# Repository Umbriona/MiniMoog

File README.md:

# MiniMoog
Minimoog clone project

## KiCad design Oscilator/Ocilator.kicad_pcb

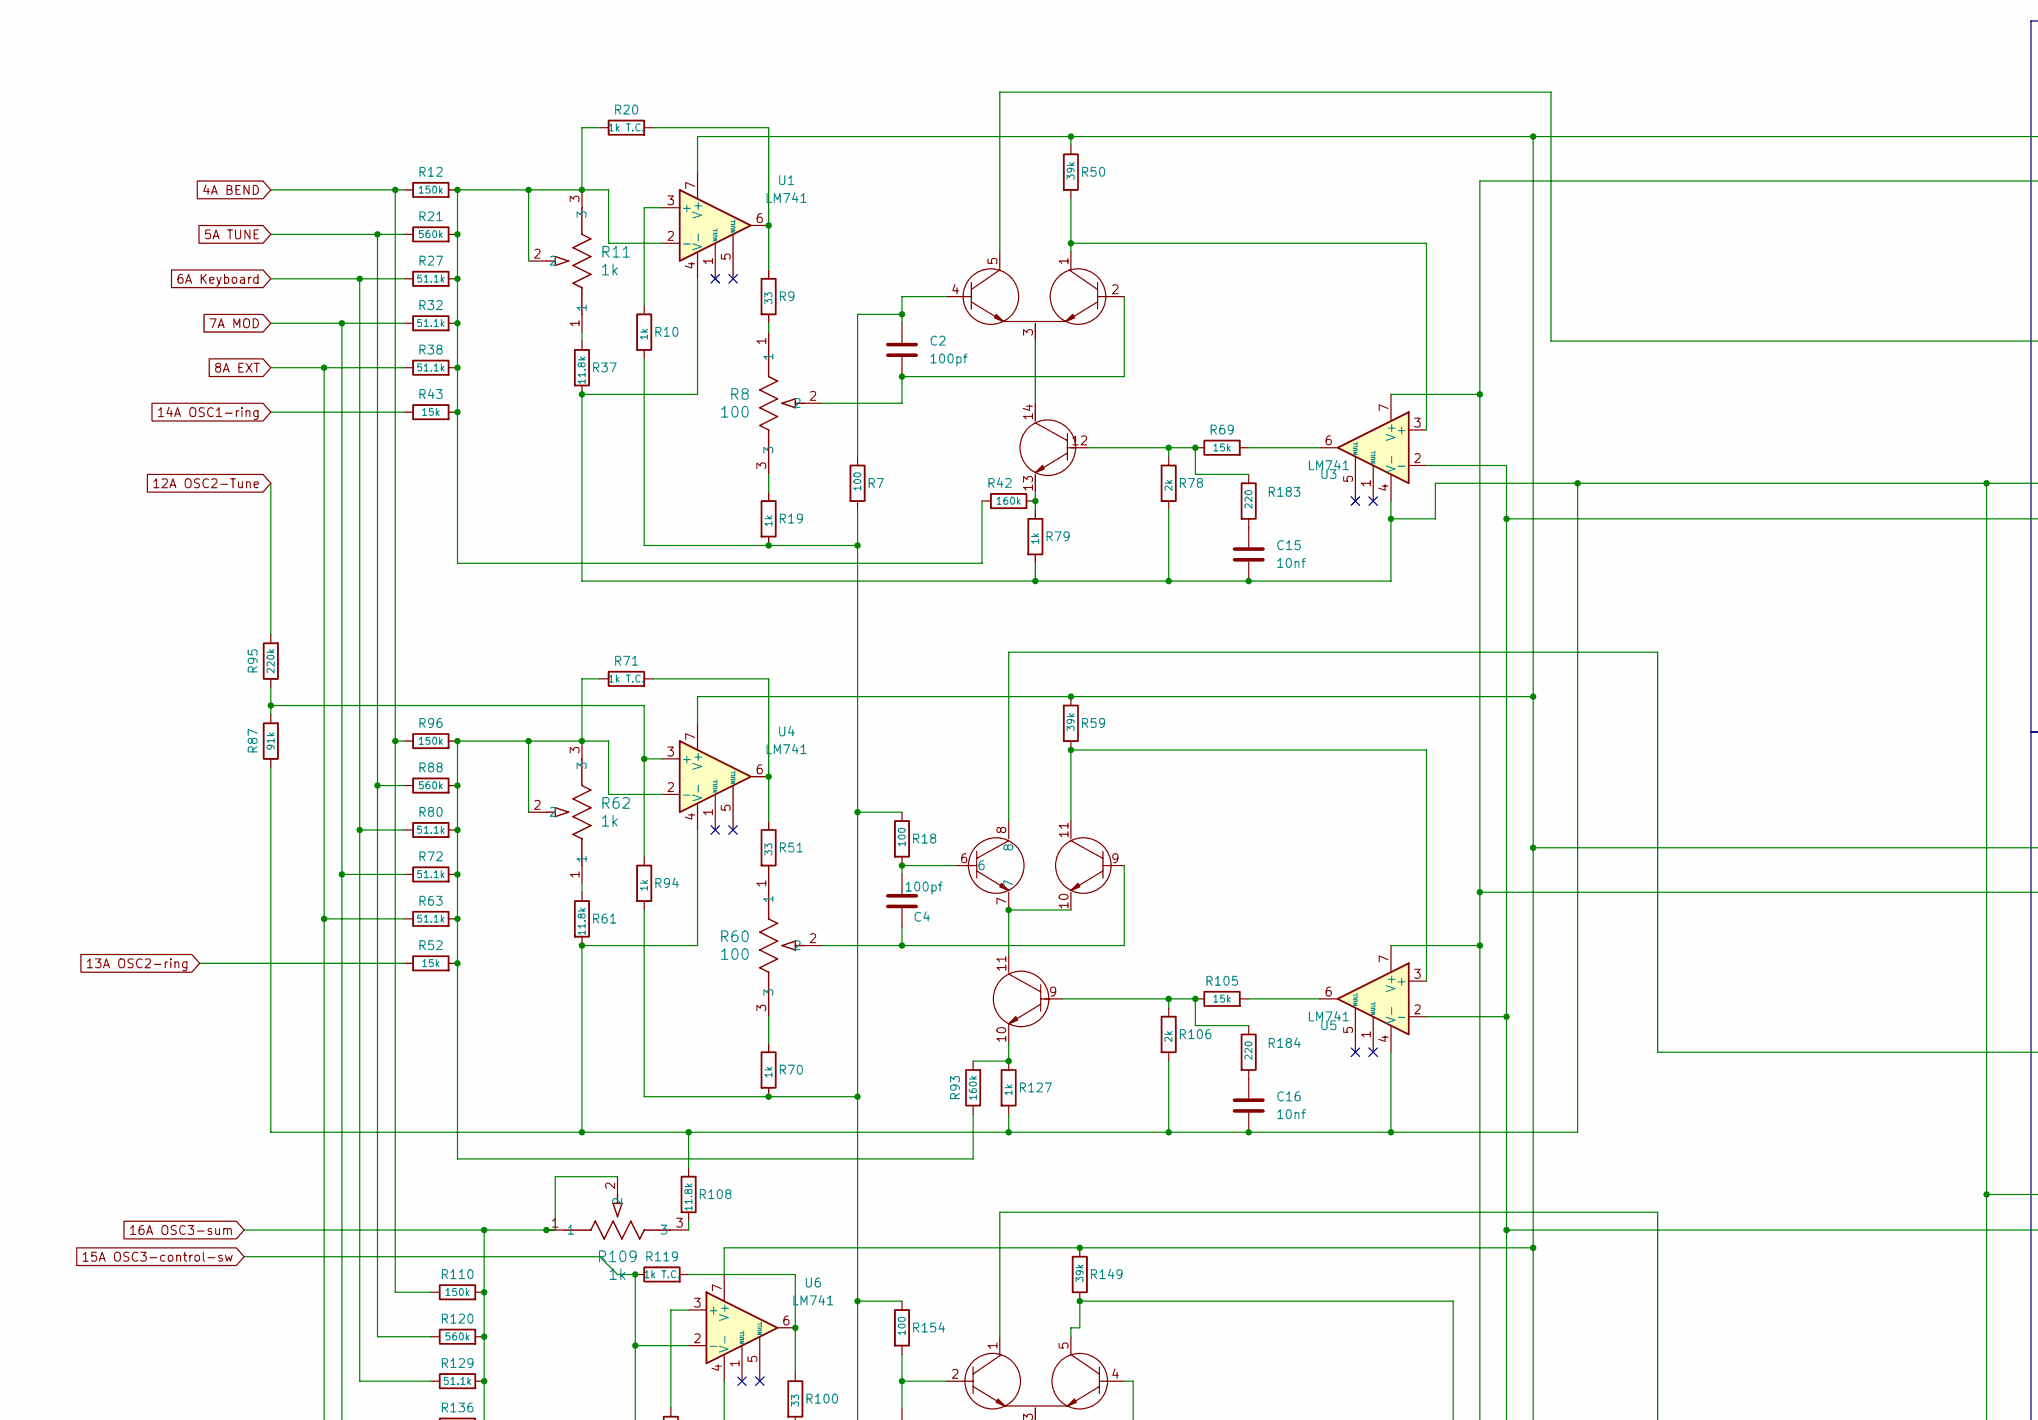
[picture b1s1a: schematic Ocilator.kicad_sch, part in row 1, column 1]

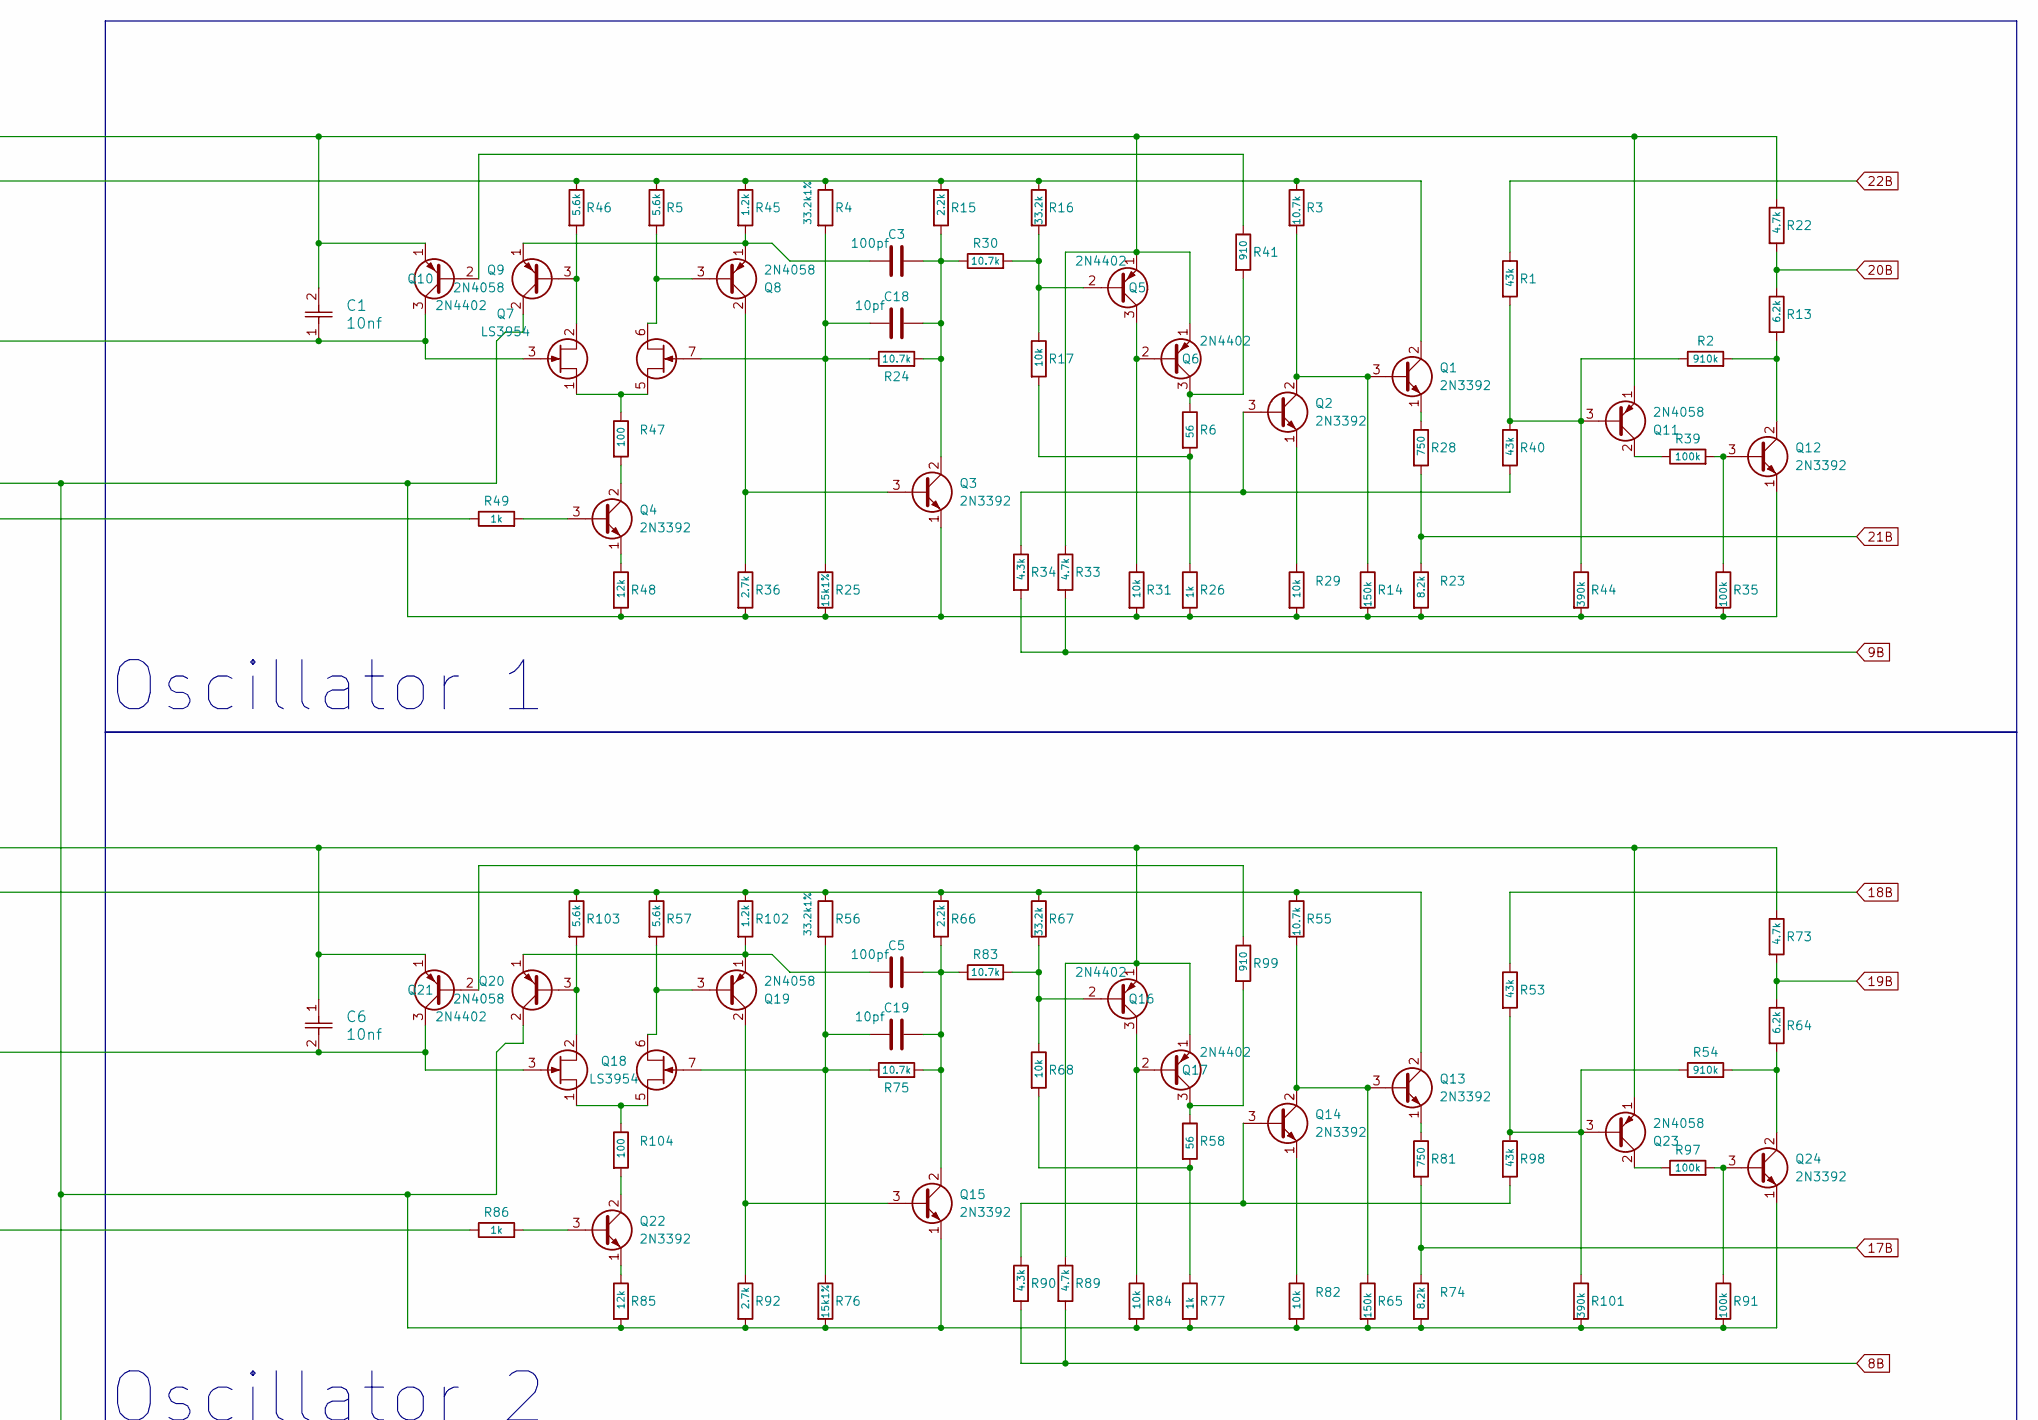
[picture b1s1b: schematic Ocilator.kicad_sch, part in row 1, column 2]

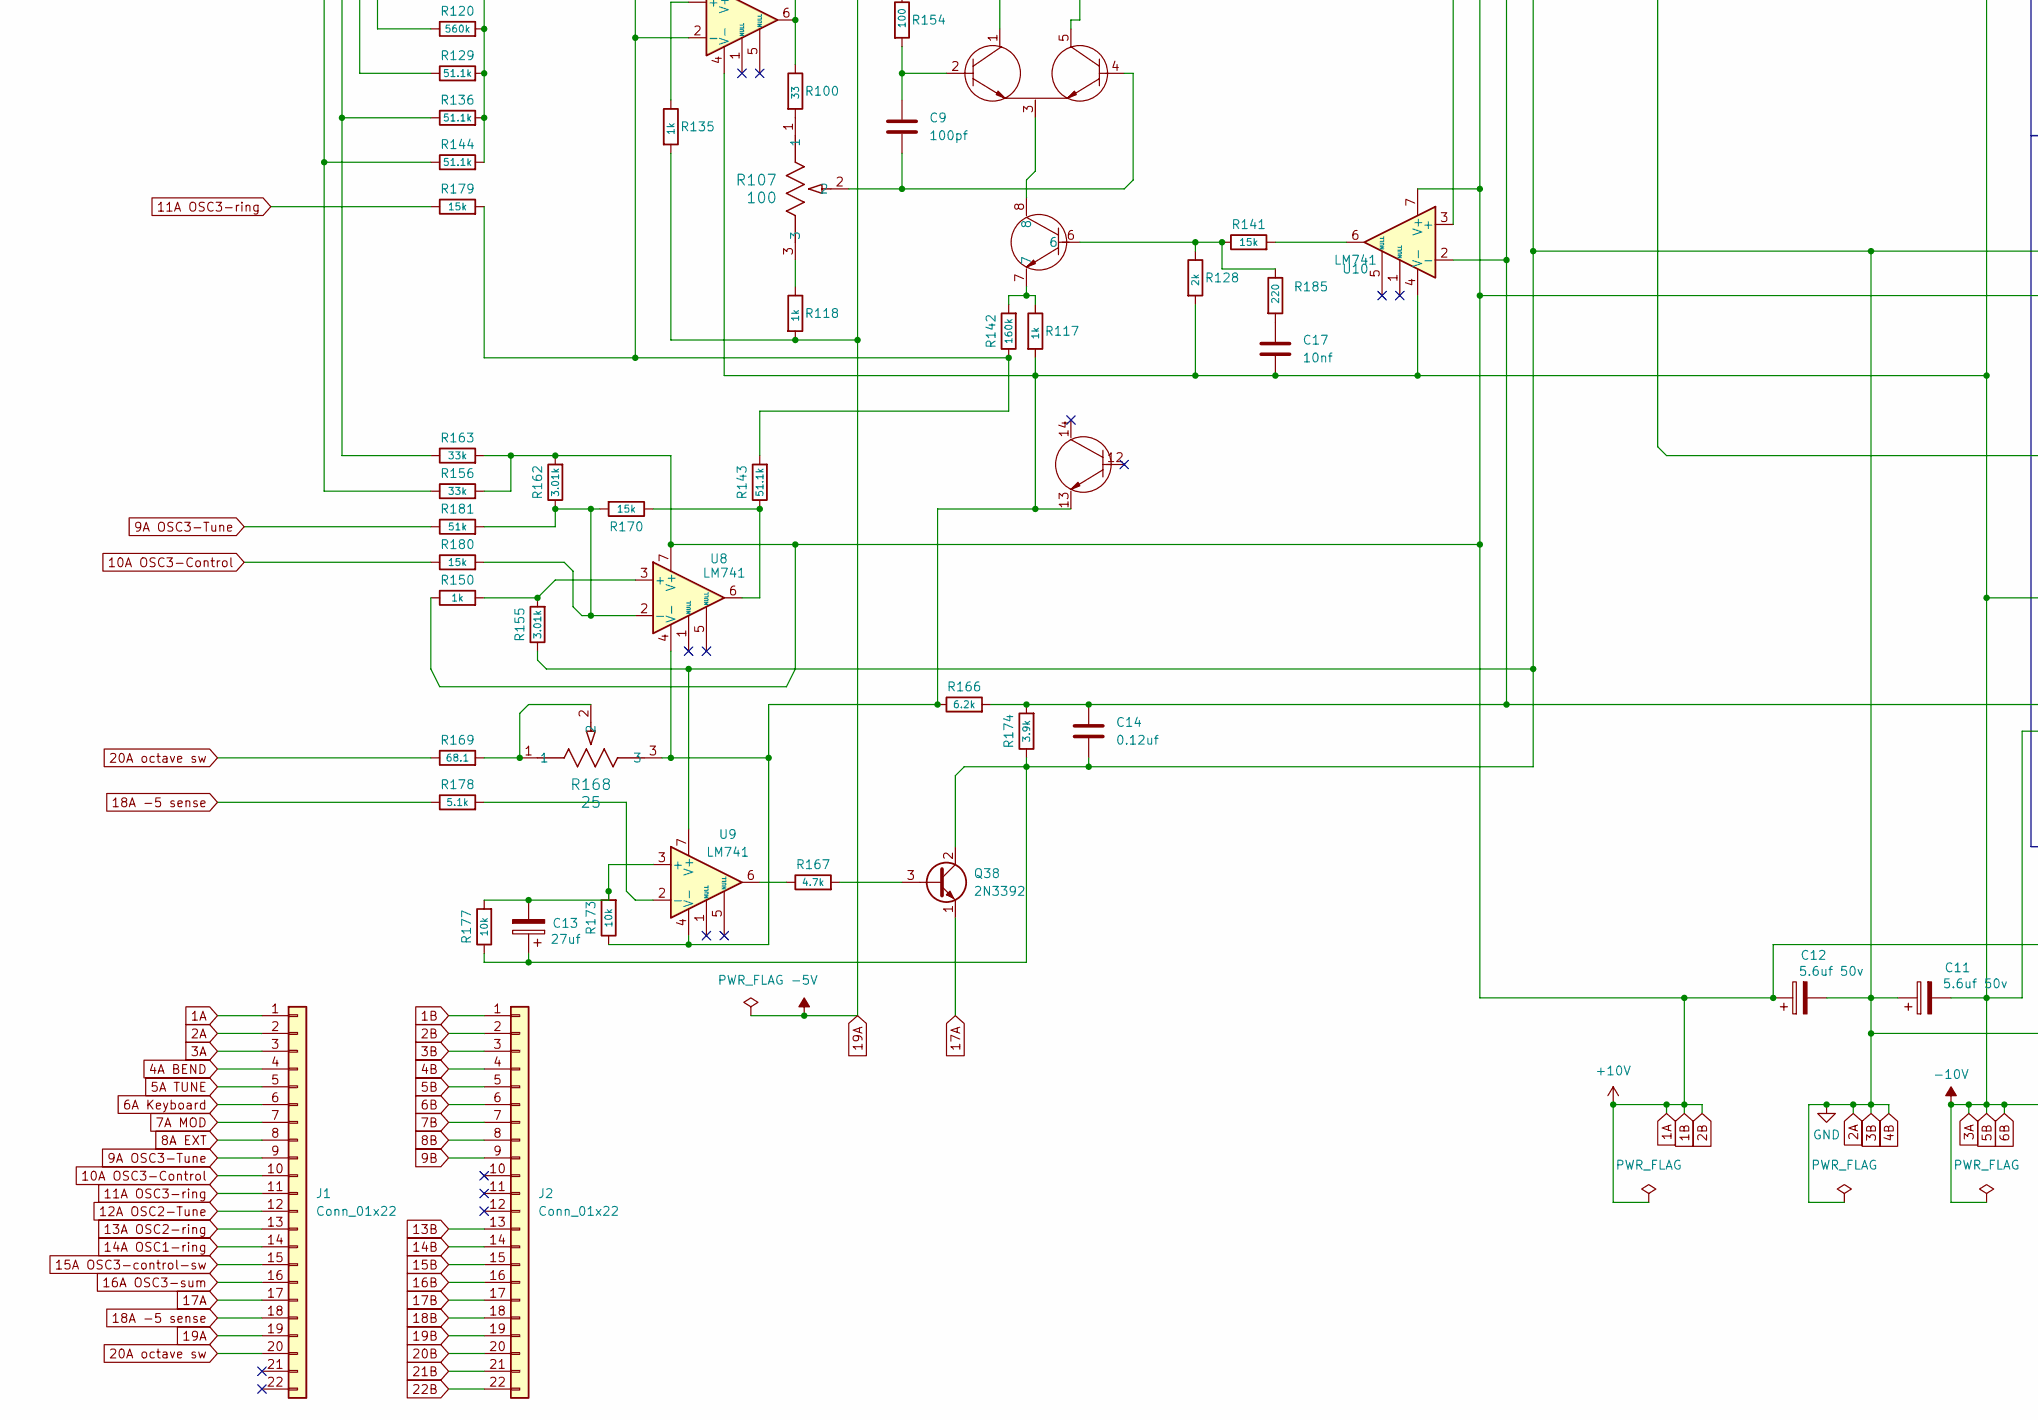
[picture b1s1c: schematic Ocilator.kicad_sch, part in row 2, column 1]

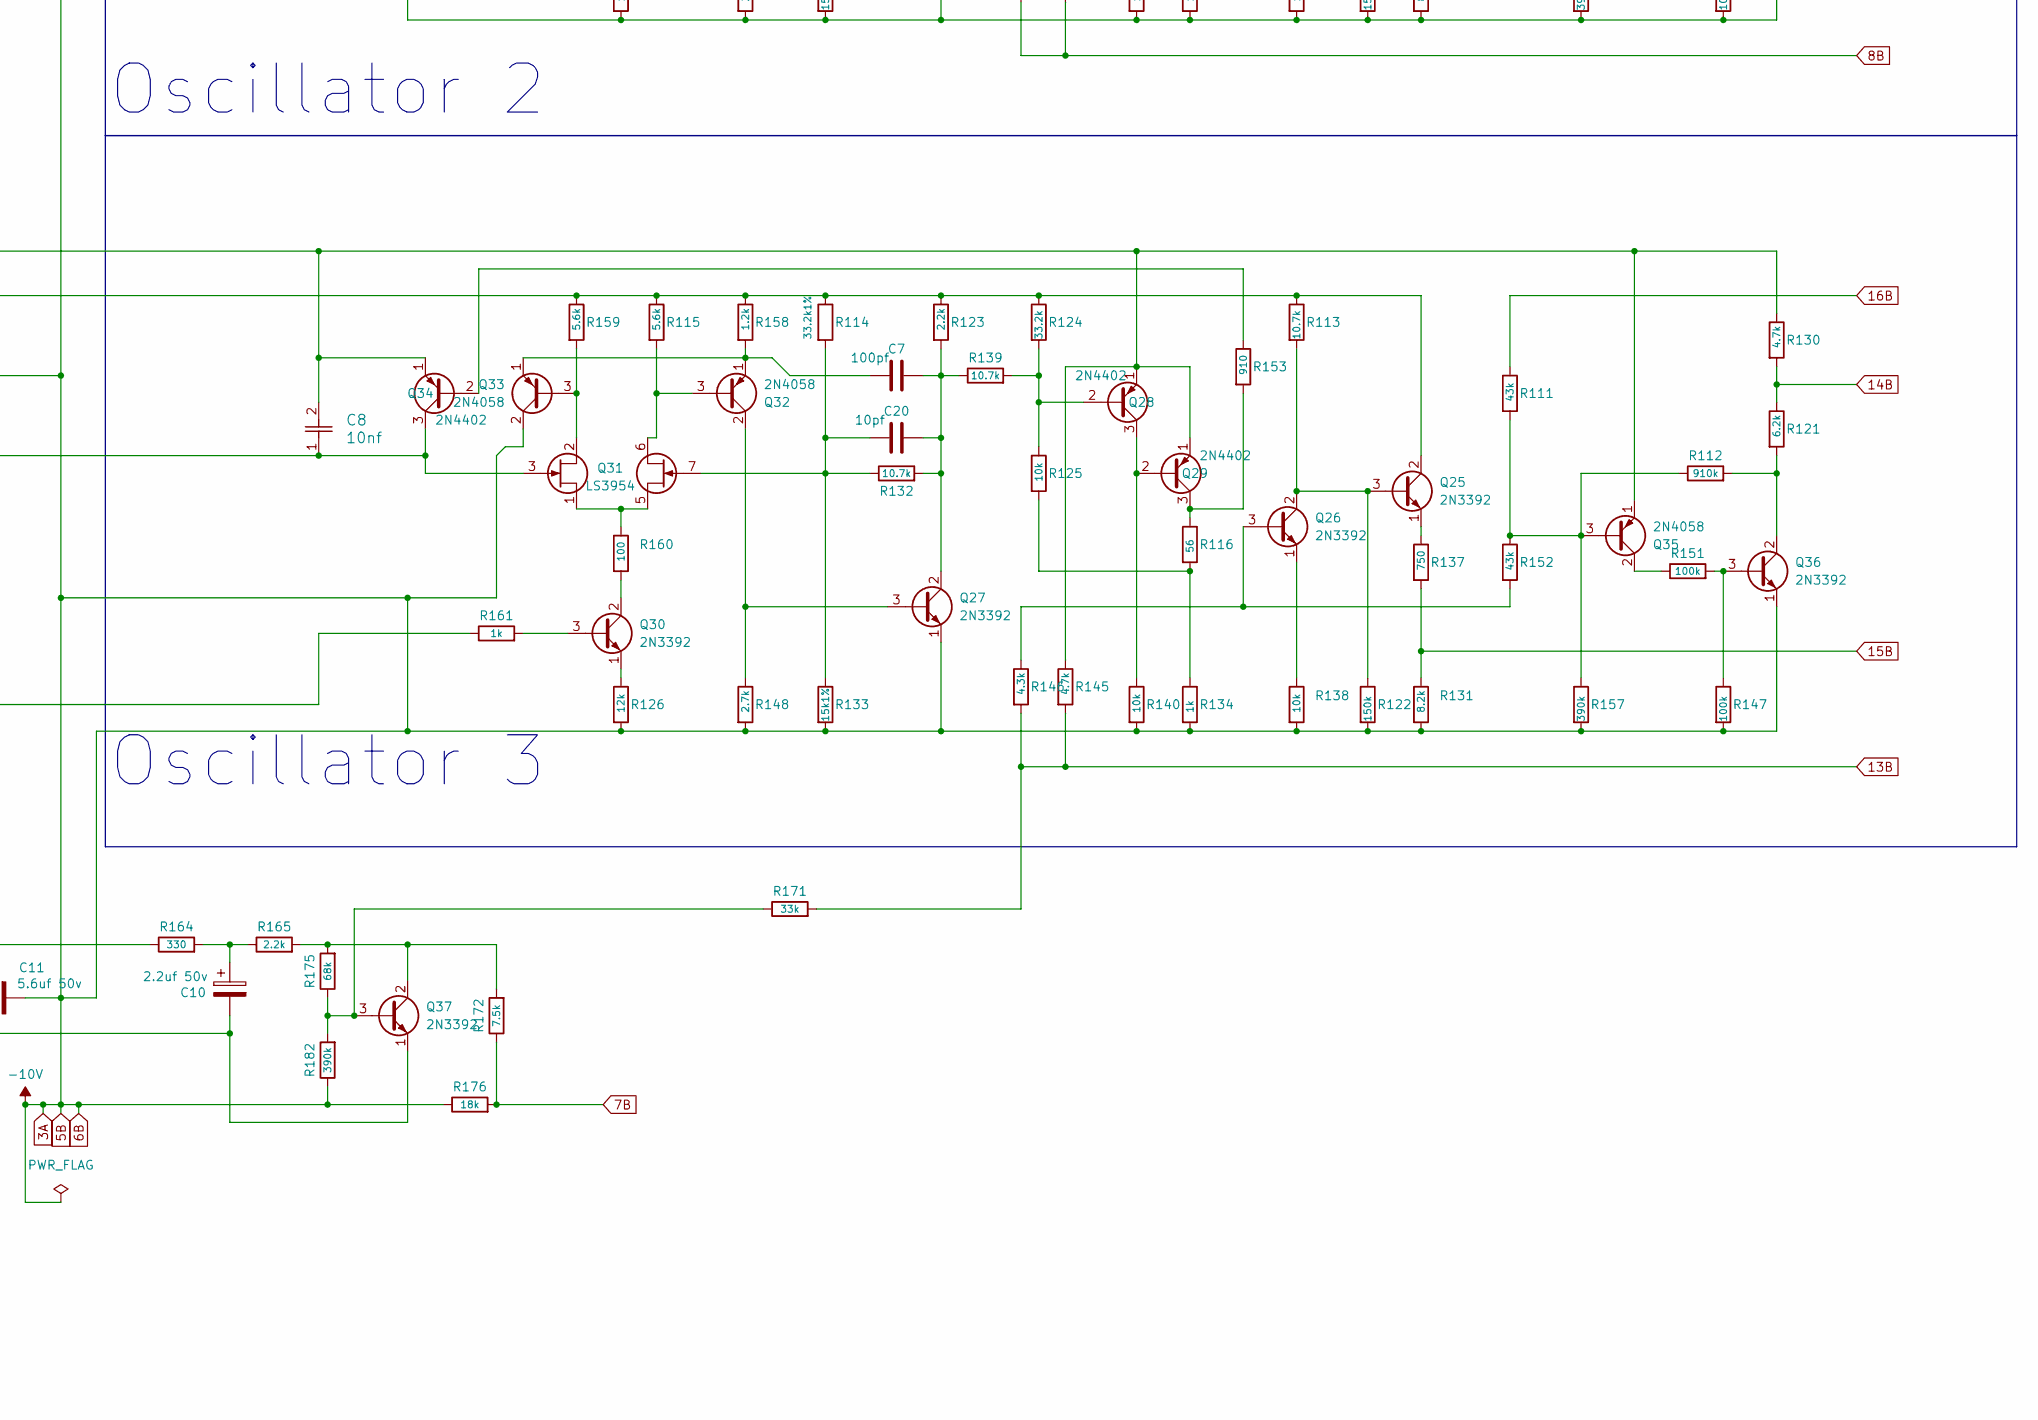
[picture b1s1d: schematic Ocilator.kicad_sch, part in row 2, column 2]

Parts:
C1, C6, C8: 10nf; CAP_MKP_416-420_05.0P_03.5WX08.0HX07.2L_VIS
C2, C7, C9: 100pf; C_Disc_D5.0mm_W2.5mm_P5.00mm
C3, C4, C5: 100pf; C_Disc_D4.7mm_W2.5mm_P5.00mm
C10: 2.2uf 50v; CP_Axial_L10.0mm_D4.5mm_P15.00mm_Horizontal
C11, C12: 5.6uf 50v; CP_Radial_Tantal_D5.0mm_P2.50mm
C13: 27uf; CP_Radial_Tantal_D9.0mm_P5.00mm
C14: 0.12uf; C_Rect_L7.0mm_W2.5mm_P5.00mm
C15, C16, C17: 10nf; Capacitor_THTC_Disc_D3.5mm_W2mm_P5.50mm
C18, C19, C20: 10pf; C_Axial_L3.8mm_D2.6mm_P7.50mm_Horizontal
J1, J2: Conn_01x22; Edge_fingers_01x22
Q1, Q2, Q3, Q4, Q12, Q13, Q14, Q15, Q22, Q24, Q25, Q26, Q27, Q30, Q36, Q37, Q38: 2N3392; TO-92_Inline
Q5, Q6, Q10, Q16, Q17, Q21, Q28, Q29, Q34: 2N4402; TO-92_Inline
Q7, Q18, Q31: LS3954; LS3955
Q8, Q9, Q11, Q19, Q20, Q23, Q32, Q33, Q35: 2N4058; TO-92_Inline
R1, R40, R53, R98, R111, R152: 43k; R_Axial_DIN0411_L9.9mm_D3.6mm_P12.70mm_Horizontal
R2, R54, R112: 910k; R_Axial_DIN0411_L9.9mm_D3.6mm_P12.70mm_Horizontal
R3, R24, R30, R55, R75, R83, R113, R132, R139: 10.7k; R_Axial_DIN0411_L9.9mm_D3.6mm_P12.70mm_Horizontal
R4, R56, R114: 33.2k1%; R_Axial_DIN0411_L9.9mm_D3.6mm_P12.70mm_Horizontal
R5, R46, R57, R103, R115, R159: 5.6k; R_Axial_DIN0411_L9.9mm_D3.6mm_P12.70mm_Horizontal
R6, R58, R116: 56; R_Axial_DIN0411_L9.9mm_D3.6mm_P12.70mm_Horizontal
R7, R18, R47, R104, R154, R160: 100; R_Axial_DIN0411_L9.9mm_D3.6mm_P12.70mm_Horizontal
R8, R60, R107: 100; POT_3296W
R9, R51, R100: 33; R_Axial_DIN0411_L9.9mm_D3.6mm_P12.70mm_Horizontal
R10, R19, R26, R49, R70, R77, R79, R86, R94, R117, R118, R127, R134, R135, R150, R161: 1k; R_Axial_DIN0411_L9.9mm_D3.6mm_P12.70mm_Horizontal
R11, R62, R109: 1k; POT_3296W
R12, R14, R65, R96, R110, R122: 150k; R_Axial_DIN0411_L9.9mm_D3.6mm_P12.70mm_Horizontal
R13, R64, R121, R166: 6.2k; R_Axial_DIN0411_L9.9mm_D3.6mm_P12.70mm_Horizontal
R15, R66, R123, R165: 2.2k; R_Axial_DIN0411_L9.9mm_D3.6mm_P12.70mm_Horizontal
R16, R67, R124: 33.2k; R_Axial_DIN0411_L9.9mm_D3.6mm_P12.70mm_Horizontal
R17, R29, R31, R68, R82, R84, R125, R138, R140, R173, R177: 10k; R_Axial_DIN0411_L9.9mm_D3.6mm_P12.70mm_Horizontal
R20, R71, R119: 1k T.C.; Resistor_THT-R_Radial_Power_L4.2mm_W2.0mm_P3.00mm
R21, R88, R120: 560k; R_Axial_DIN0411_L9.9mm_D3.6mm_P12.70mm_Horizontal
R22, R33, R73, R89, R130, R145, R167: 4.7k; R_Axial_DIN0411_L9.9mm_D3.6mm_P12.70mm_Horizontal
R23, R74, R131: 8.2k; R_Axial_DIN0411_L9.9mm_D3.6mm_P12.70mm_Horizontal
R25, R76, R133: 15k1%; R_Axial_DIN0411_L9.9mm_D3.6mm_P12.70mm_Horizontal
R27, R32, R38, R63, R72, R80, R129, R136, R143, R144: 51.1k; R_Axial_DIN0411_L9.9mm_D3.6mm_P12.70mm_Horizontal
R28, R81, R137: 750; R_Axial_DIN0411_L9.9mm_D3.6mm_P12.70mm_Horizontal
R34, R90, R146: 4.3k; R_Axial_DIN0411_L9.9mm_D3.6mm_P12.70mm_Horizontal
R35, R39, R91, R97, R147, R151: 100k; R_Axial_DIN0411_L9.9mm_D3.6mm_P12.70mm_Horizontal
R36, R92, R148: 2.7k; R_Axial_DIN0411_L9.9mm_D3.6mm_P12.70mm_Horizontal
R37, R61, R108: 11.8k; R_Axial_DIN0411_L9.9mm_D3.6mm_P12.70mm_Horizontal
R41, R99, R153: 910; R_Axial_DIN0411_L9.9mm_D3.6mm_P12.70mm_Horizontal
R42, R93, R142: 160k; R_Axial_DIN0411_L9.9mm_D3.6mm_P12.70mm_Horizontal
R43, R52, R69, R105, R141, R170, R179, R180: 15k; R_Axial_DIN0411_L9.9mm_D3.6mm_P12.70mm_Horizontal
R44, R101, R157, R182: 390k; R_Axial_DIN0411_L9.9mm_D3.6mm_P12.70mm_Horizontal
R45, R102, R158: 1.2k; R_Axial_DIN0411_L9.9mm_D3.6mm_P12.70mm_Horizontal
R48, R85, R126: 12k; R_Axial_DIN0411_L9.9mm_D3.6mm_P12.70mm_Horizontal
R50, R59, R149: 39k; R_Axial_DIN0411_L9.9mm_D3.6mm_P12.70mm_Horizontal
R78, R106, R128: 2k; R_Axial_DIN0411_L9.9mm_D3.6mm_P12.70mm_Horizontal
R87: 91k; R_Axial_DIN0411_L9.9mm_D3.6mm_P12.70mm_Horizontal
R95: 220k; R_Axial_DIN0411_L9.9mm_D3.6mm_P12.70mm_Horizontal
R155, R162: 3.01k; R_Axial_DIN0411_L9.9mm_D3.6mm_P12.70mm_Horizontal
R156, R163, R171: 33k; R_Axial_DIN0411_L9.9mm_D3.6mm_P12.70mm_Horizontal
R164: 330; R_Axial_DIN0411_L9.9mm_D3.6mm_P12.70mm_Horizontal
R168: 25; POT_3296W
R169: 68.1; R_Axial_DIN0411_L9.9mm_D3.6mm_P12.70mm_Horizontal
R172: 7.5k; R_Axial_DIN0411_L9.9mm_D3.6mm_P12.70mm_Horizontal
R174: 3.9k; R_Axial_DIN0411_L9.9mm_D3.6mm_P12.70mm_Horizontal
R175: 68k; R_Axial_DIN0411_L9.9mm_D3.6mm_P12.70mm_Horizontal
R176: 18k; R_Axial_DIN0411_L9.9mm_D3.6mm_P12.70mm_Horizontal
R178: 5.1k; R_Axial_DIN0411_L9.9mm_D3.6mm_P12.70mm_Horizontal
R181: 51k; R_Axial_DIN0411_L9.9mm_D3.6mm_P12.70mm_Horizontal
R183, R184, R185: 220; R_Axial_DIN0411_L9.9mm_D3.6mm_P12.70mm_Horizontal
U1, U3, U4, U5, U6, U8, U9, U10: LM741; DIP-8_W7.62mm
U2, U7: Ca3046; CERDIP-14_W7.62mm_SideBrazed

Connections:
1A: C12.1, J1.1, J2.1, J2.2, Q1.2 (C), Q13.2 (C), Q25.2 (C), R3.1, R4.1, R5.1, R15.1, R16.1, R45.1, R46.1, R55.1, R56.1, R57.1, R66.1, R67.1, R102.1, R103.1, R113.1, R114.1, R115.1, R123.1, R124.1, R150.1, R156.2, R158.1, R159.1, R162.2, R163.2, R164.1, U3.7 (V+), U5.7 (V+), U8.7 (V+), U10.7 (V+)
2A: C1.2, C6.1, C8.2, C10.2, C11.1, C12.2, C13.1, C14.2, J1.2, J2.3, J2.4, Q5.1 (E), Q6.1 (E), Q10.1 (E), Q11.1 (E), Q16.1 (E), Q17.1 (E), Q21.1 (E), Q23.1 (E), Q28.1 (E), Q29.1 (E), Q34.1 (E), Q35.1 (E), Q37.1 (E), Q38.2 (C), R22.1, R33.1, R50.1, R59.1, R73.1, R89.1, R130.1, R145.1, R149.1, R155.1, R174.1, R177.1, U1.7 (V+), U4.7 (V+), U6.7 (V+), U9.7 (V+)
3A: C11.2, C15.2, C16.2, C17.2, J1.3, J2.5, J2.6, Q3.1 (E), Q9.2 (C), Q12.1 (E), Q15.1 (E), Q20.2 (C), Q24.1 (E), Q27.1 (E), Q33.2 (C), Q36.1 (E), R14.2, R23.2, R25.2, R26.2, R29.2, R31.2, R35.2, R36.2, R37.2, R44.2, R48.2, R61.2, R65.2, R74.2, R76.2, R77.2, R78.2, R79.2, R82.2, R84.2, R85.2, R87.1, R91.2, R92.2, R101.2, R106.2, R108.1, R117.2, R122.2, R126.2, R127.2, R128.2, R131.2, R133.2, R134.2, R138.2, R140.2, R147.2, R148.2, R157.2, R166.1, R168.3, R173.1, R176.1, R182.1, U1.4 (V-), U3.4 (V-), U4.4 (V-), U5.4 (V-), U6.4 (V-), U7.13, U8.4 (V-), U9.4 (V-), U10.4 (V-)
4A BEND: J1.4, R12.1, R96.1, R110.1
5A TUNE: J1.5, R21.1, R88.1, R120.1
6A Keyboard: J1.6, R27.1, R80.1, R129.1
7A MOD: J1.7, R32.1, R72.1, R136.1, R163.1
7B: J2.7, R172.1, R176.2
8A EXT: J1.8, R38.1, R63.1, R144.1, R156.1
8B: J2.8, R89.2, R90.2
9A OSC3-Tune: J1.9, R181.1
9B: J2.9, R33.2, R34.2
10A OSC3-Control: J1.10, R180.1
11A OSC3-ring: J1.11, R179.1
12A OSC2-Tune: J1.12, R95.2
13A OSC2-ring: J1.13, R52.1
13B: J2.13, R145.2, R146.2, R171.2
14A OSC1-ring: J1.14, R43.1
14B: J2.14, R121.1, R130.2
15A OSC3-control-sw: J1.15, R119.1, R142.1, R143.2, R179.2, U6.2 (-)
15B: J2.15, R131.1, R137.2
16A OSC3-sum: J1.16, R109.1, R109.2, R110.2, R120.2, R129.2, R136.2, R144.2
16B: J2.16, R111.1
17A: J1.17, Q38.1 (E)
17B: J2.17, R74.1, R81.2
18A -5 sense: J1.18, R178.1
18B: J2.18, R53.1
19A: J1.19, R7.2, R10.2, R18.1, R19.2, R70.2, R94.2, R118.2, R135.2, R154.1
19B: J2.19, R64.1, R73.2
20A octave sw: J1.20, R169.1
20B: J2.20, R13.1, R22.2
21B: J2.21, R23.1, R28.2
22B: J2.22, R1.1
unnamed: C2.1, R7.1, U2.4
unnamed: C2.2, R8.2, U2.2
unnamed: C4.1, R18.2, U2.6
unnamed: C4.2, R60.2, U2.9
unnamed: C9.1, R154.2, U7.2
unnamed: C9.2, R107.2, U7.4
unnamed: C10.1, R164.2, R165.1
unnamed: C15.1, R183.2
unnamed: C16.1, R184.2
unnamed: C17.1, R185.2
unnamed: Q1.3 (B), Q2.2 (C), R3.2, R14.1
unnamed: Q1.1 (E), R28.1
unnamed: Q2.3 (B), R34.1, R40.2
unnamed: Q2.1 (E), R29.1
unnamed: Q3.3 (B), Q8.2 (C), R36.1
unnamed: C3.2, C18.2, Q3.2 (C), R15.2, R24.2, R30.1
unnamed: Q4.3 (B), R49.2
unnamed: Q4.2 (C), R47.2
unnamed: Q4.1 (E), R48.1
unnamed: Q5.2 (B), R16.2, R17.1, R30.2
unnamed: Q5.3 (C), Q6.2 (B), R31.1
unnamed: Q6.3 (C), R6.1, R41.2
unnamed: Q7.2 (D1), Q9.3 (B), R46.2
unnamed: Q7.6 (D2), Q8.3 (B), R5.2
unnamed: C18.1, Q7.7 (G2), R4.2, R24.1, R25.1
unnamed: Q7.1 (S1), Q7.5 (S2), R47.1
unnamed: C3.1, Q8.1 (E), Q9.1 (E), R45.2
unnamed: Q10.2 (B), R41.1
unnamed: C1.1, Q7.3 (G1), Q10.3 (C), U2.5
unnamed: Q11.3 (B), R1.2, R2.1, R40.1, R44.1
unnamed: Q11.2 (C), R39.1
unnamed: Q12.3 (B), R35.1, R39.2
unnamed: Q12.2 (C), R2.2, R13.2
unnamed: Q13.3 (B), Q14.2 (C), R55.2, R65.1
unnamed: Q13.1 (E), R81.1
unnamed: Q14.3 (B), R90.1, R98.2
unnamed: Q14.1 (E), R82.1
unnamed: Q15.3 (B), Q19.2 (C), R92.1
unnamed: C5.2, C19.2, Q15.2 (C), R66.2, R75.2, R83.1
unnamed: Q16.2 (B), R67.2, R68.1, R83.2
unnamed: Q16.3 (C), Q17.2 (B), R84.1
unnamed: Q17.3 (C), R58.1, R99.2
unnamed: Q18.2 (D1), Q20.3 (B), R103.2
unnamed: Q18.6 (D2), Q19.3 (B), R57.2
unnamed: C6.2, Q18.3 (G1), Q21.3 (C), U2.8
unnamed: C19.1, Q18.7 (G2), R56.2, R75.1, R76.1
unnamed: Q18.1 (S1), Q18.5 (S2), R104.1
unnamed: C5.1, Q19.1 (E), Q20.1 (E), R102.2
unnamed: Q21.2 (B), R99.1
unnamed: Q22.3 (B), R86.2
unnamed: Q22.2 (C), R104.2
unnamed: Q22.1 (E), R85.1
unnamed: Q23.3 (B), R53.2, R54.1, R98.1, R101.1
unnamed: Q23.2 (C), R97.1
unnamed: Q24.3 (B), R91.1, R97.2
unnamed: Q24.2 (C), R54.2, R64.2
unnamed: Q25.3 (B), Q26.2 (C), R113.2, R122.1
unnamed: Q25.1 (E), R137.1
unnamed: Q26.3 (B), R146.1, R152.2
unnamed: Q26.1 (E), R138.1
unnamed: Q27.3 (B), Q32.2 (C), R148.1
unnamed: C7.2, C20.2, Q27.2 (C), R123.2, R132.2, R139.1
unnamed: Q28.2 (B), R124.2, R125.1, R139.2
unnamed: Q28.3 (C), Q29.2 (B), R140.1
unnamed: Q29.3 (C), R116.1, R153.2
unnamed: Q30.3 (B), R161.2
unnamed: Q30.2 (C), R160.2
unnamed: Q30.1 (E), R126.1
unnamed: Q31.2 (D1), Q33.3 (B), R159.2
unnamed: Q31.6 (D2), Q32.3 (B), R115.2
unnamed: C8.1, Q31.3 (G1), Q34.3 (C), U7.1
unnamed: C20.1, Q31.7 (G2), R114.2, R132.1, R133.1
unnamed: Q31.1 (S1), Q31.5 (S2), R160.1
unnamed: C7.1, Q32.1 (E), Q33.1 (E), R158.2
unnamed: Q34.2 (B), R153.1
unnamed: Q35.3 (B), R111.2, R112.1, R152.1, R157.1
unnamed: Q35.2 (C), R151.1
unnamed: Q36.3 (B), R147.1, R151.2
unnamed: Q36.2 (C), R112.2, R121.2
unnamed: Q37.3 (B), R171.1, R175.1, R182.2
unnamed: Q37.2 (C), R165.2, R172.2, R175.2
unnamed: Q38.3 (B), R167.2
unnamed: R8.1, R9.2
unnamed: R11.1, R37.1
unnamed: R6.2, R17.2, R26.1
unnamed: R8.3, R19.1
unnamed: R9.1, R20.2, U1.6
unnamed: R42.2, R79.1, U2.13
unnamed: R51.1, R71.2, U4.6
unnamed: R51.2, R60.1
unnamed: R58.2, R68.2, R77.1
unnamed: R60.3, R70.1
unnamed: R61.1, R62.1
unnamed: R69.2, U3.6
unnamed: R100.1, R119.2, U6.6
unnamed: R100.2, R107.1
unnamed: R105.1, R106.1, R184.1, U7.9
unnamed: R105.2, U5.6
unnamed: R107.3, R118.1
unnamed: R108.2, R109.3
unnamed: R116.2, R125.2, R134.1
unnamed: R117.1, R142.2, U7.7
unnamed: R93.2, R127.1, U7.10
unnamed: R128.1, R141.1, R185.1, U7.6
unnamed: R141.2, U10.6
unnamed: R143.1, R170.1, U8.6
unnamed: R167.1, U9.6
unnamed: R168.1, R168.2, R169.2
unnamed: R69.1, R78.1, R183.1, U2.12
unnamed: R10.1, U1.3 (+)
unnamed: R11.2, R11.3, R12.2, R20.1, R21.2, R27.2, R32.2, R38.2, R42.1, R43.2, U1.2 (-)
unnamed: U2.7, U2.10, U7.11
unnamed: U2.3, U2.14
unnamed: R50.2, U2.1, U3.3 (+)
unnamed: R87.2, R94.1, R95.1, U4.3 (+)
unnamed: R52.2, R62.2, R62.3, R63.2, R71.1, R72.2, R80.2, R88.2, R93.1, R96.2, U4.2 (-)
unnamed: R59.2, U2.11, U5.3 (+)
unnamed: R135.1, U6.3 (+)
unnamed: U7.3, U7.8
unnamed: R150.2, R155.2, U8.3 (+)
unnamed: R162.1, R170.2, R180.2, R181.2, U8.2 (-)
unnamed: C13.2, R173.2, R177.2, U9.3 (+)
unnamed: R178.2, U9.2 (-)
unnamed: R149.2, U7.5, U10.3 (+)
unnamed: C14.1, R49.1, R86.1, R161.1, R166.2, R174.2, U3.2 (-), U5.2 (-), U10.2 (-)

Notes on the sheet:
Oscillator 1
Oscillator 3
Oscillator 2

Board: 2 copper layers, 255 parts (0 on the bottom side), 158 nets, no tracks yet.
